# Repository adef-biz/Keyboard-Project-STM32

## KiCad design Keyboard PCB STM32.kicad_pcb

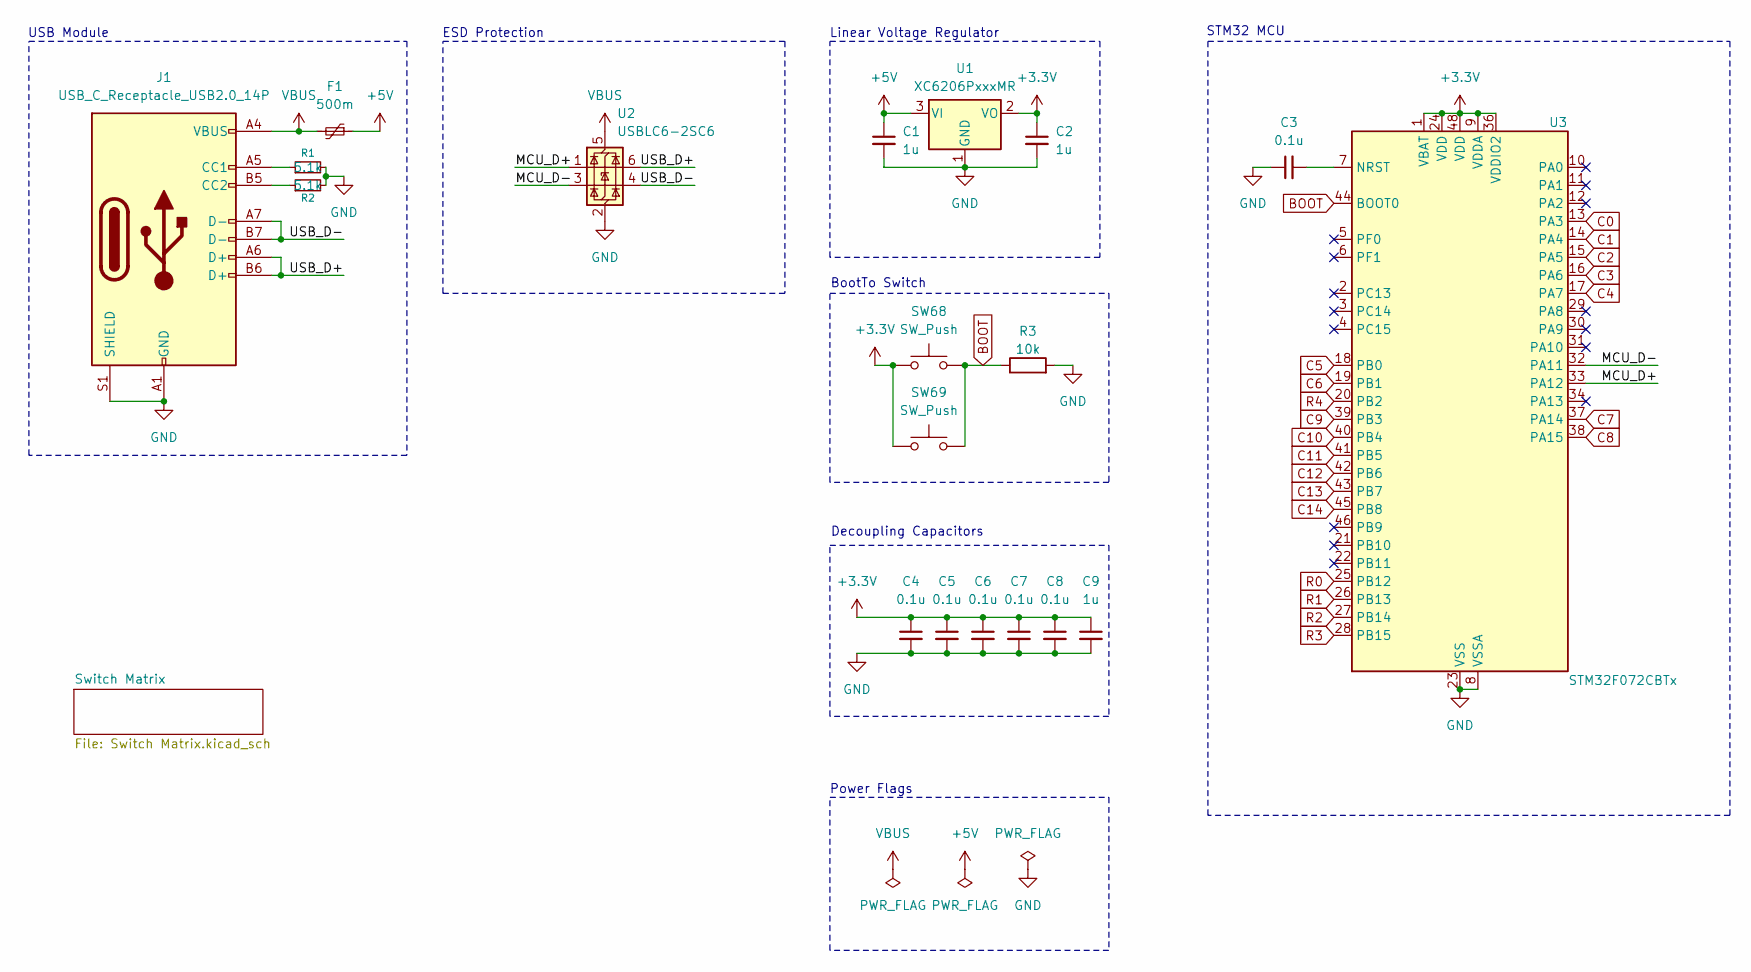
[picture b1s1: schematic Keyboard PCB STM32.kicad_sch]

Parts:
C1, C2, C9: 1u; C_0805_2012Metric
C3, C4, C5, C6, C7, C8: 0.1u; C_0805_2012Metric
F1: 500m; Fuse_1206_3216Metric
J1: USB_C_Receptacle_USB2.0_14P; USB_C_Receptacle_HRO_TYPE-C-31-M-12
R1, R2: 5.1k; R_0805_2012Metric
R3: 10k; R_0805_2012Metric
SW68: SW_Push; Panasonic_EVQPUL_EVQPUC
SW69: SW_Push; SW_Push_1P1T_XKB_TS-1187A
U1: XC6206PxxxMR; SOT-23-3
U2: USBLC6-2SC6; SOT-23-6
U3: STM32F072CBTx; LQFP-48_7x7mm_P0.5mm

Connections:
+3.3V: C2.1, C4.1, C5.1, C6.1, C7.1, C8.1, C9.1, SW68.1, SW69.1, U1.2 (VO), U3.1 (VBAT), U3.9 (VDDA), U3.24 (VDD), U3.36 (VDDIO2), U3.48 (VDD)
+5V: C1.1, F1.1, U1.3 (VI)
/MCU_D+: U2.1 (I/O1), U3.33 (PA12)
/MCU_D-: U2.3 (I/O2), U3.32 (PA11)
/USB_D+: J1.A6 (D+), J1.B6 (D+), U2.6 (I/O1)
/USB_D-: J1.A7 (D-), J1.B7 (D-), U2.4 (I/O2)
BOOT: R3.1, SW68.2, SW69.2, U3.44 (BOOT0)
C0: U3.13 (PA3); also elsewhere on the board
C1: U3.14 (PA4); also elsewhere on the board
C2: U3.15 (PA5); also elsewhere on the board
C3: U3.16 (PA6); also elsewhere on the board
C4: U3.17 (PA7); also elsewhere on the board
C5: U3.18 (PB0); also elsewhere on the board
C6: U3.19 (PB1); also elsewhere on the board
C7: U3.37 (PA14); also elsewhere on the board
C8: U3.38 (PA15); also elsewhere on the board
C9: U3.39 (PB3); also elsewhere on the board
C10: U3.40 (PB4); also elsewhere on the board
C11: U3.41 (PB5); also elsewhere on the board
C12: U3.42 (PB6); also elsewhere on the board
C13: U3.43 (PB7); also elsewhere on the board
C14: U3.45 (PB8); also elsewhere on the board
GND: C1.2, C2.2, C3.1, C4.2, C5.2, C6.2, C7.2, C8.2, C9.2, J1.A1 (GND), J1.A12 (GND), J1.B1 (GND), J1.B12 (GND), J1.S1 (SHIELD), R1.2, R2.2, R3.2, U1.1 (GND), U2.2 (GND), U3.8 (VSSA), U3.23 (VSS), U3.35 (VSS), U3.47 (VSS)
unnamed: J1.A5 (CC1), R1.1
unnamed: J1.B5 (CC2), R2.1
unnamed: C3.2, U3.7 (NRST)
R0: U3.25 (PB12); also elsewhere on the board
R1: U3.26 (PB13); also elsewhere on the board
R2: U3.27 (PB14); also elsewhere on the board
R3: U3.28 (PB15); also elsewhere on the board
R4: U3.20 (PB2); also elsewhere on the board
VBUS: F1.2, J1.A4 (VBUS), J1.A9 (VBUS), J1.B4 (VBUS), J1.B9 (VBUS), U2.5 (VBUS)

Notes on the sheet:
BootTo Switch
USB Module
ESD Protection
Linear Voltage Regulator
Decoupling Capacitors
Power Flags
STM32 MCU

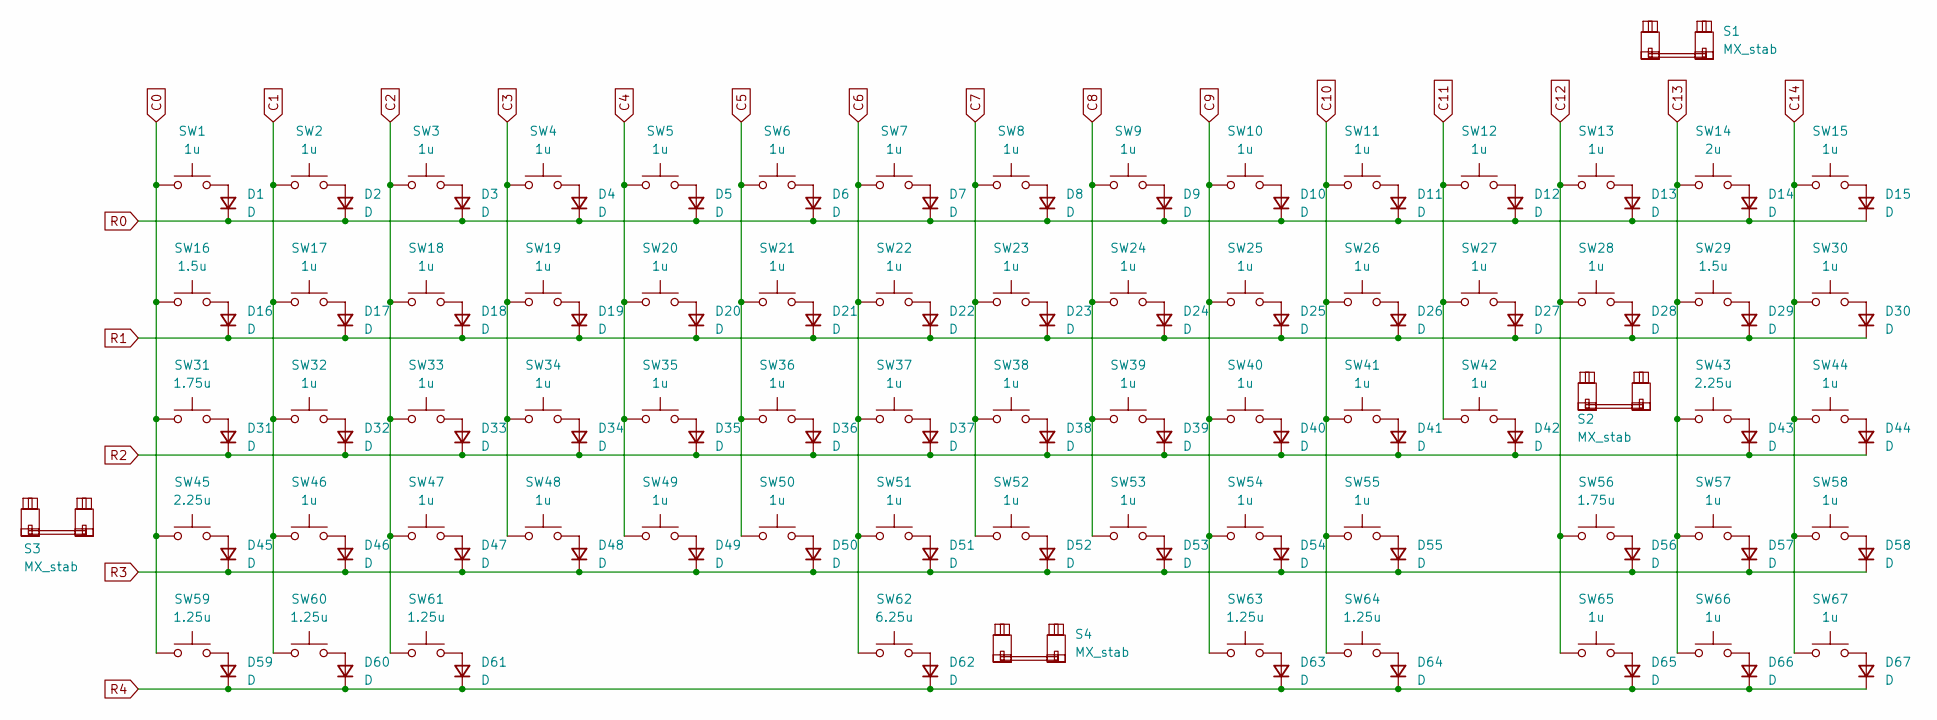
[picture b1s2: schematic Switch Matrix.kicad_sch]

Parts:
D1, D2, D3, D4, D5, D6, D7, D8, D9, D10, D11, D12, D13, D14, D15, D16, D17, D18, D19, D20, D21, D22, D23, D24, D25, D26, D27, D28, D29, D30, D31, D32, D33, D34, D35, D36, D37, D38, D39, D40, D41, D42, D43, D44, D45, D46, D47, D48, D49, D50, D51, D52, D53, D54, D55, D56, D57, D58, D59, D60, D61, D62, D63, D64, D65, D66, D67: D; D_SOD-123
S1: MX_stab; STAB_MX_2u
S2, S3: MX_stab; STAB_MX_2.25u
S4: MX_stab; STAB_MX_6.25u
SW1, SW2, SW3, SW4, SW5, SW6, SW7, SW8, SW9, SW10, SW11, SW12, SW13, SW15, SW17, SW18, SW19, SW20, SW21, SW22, SW23, SW24, SW25, SW26, SW27, SW28, SW30, SW32, SW33, SW34, SW35, SW36, SW37, SW38, SW39, SW40, SW41, SW42, SW44, SW46, SW47, SW48, SW49, SW50, SW51, SW52, SW53, SW54, SW55, SW57, SW58, SW65, SW66, SW67: 1u; SW_MX_1u
SW14: 2u; SW_MX_1u
SW16, SW29: 1.5u; SW_MX_1.5u
SW31, SW56: 1.75u; SW_MX_1.75u
SW43, SW45: 2.25u; SW_MX_1u
SW59, SW60, SW61, SW63, SW64: 1.25u; SW_MX_1.25u
SW62: 6.25u; SW_MX_1u

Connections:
C0: SW1.1, SW16.1, SW31.1, SW45.1, SW59.1; also elsewhere on the board
C1: SW2.1, SW17.1, SW32.1, SW46.1, SW60.1; also elsewhere on the board
C2: SW3.1, SW18.1, SW33.1, SW47.1, SW61.1; also elsewhere on the board
C3: SW4.1, SW19.1, SW34.1, SW48.1; also elsewhere on the board
C4: SW5.1, SW20.1, SW35.1, SW49.1; also elsewhere on the board
C5: SW6.1, SW21.1, SW36.1, SW50.1; also elsewhere on the board
C6: SW7.1, SW22.1, SW37.1, SW51.1, SW62.1; also elsewhere on the board
C7: SW8.1, SW23.1, SW38.1, SW52.1; also elsewhere on the board
C8: SW9.1, SW24.1, SW39.1, SW53.1; also elsewhere on the board
C9: SW10.1, SW25.1, SW40.1, SW54.1, SW63.1; also elsewhere on the board
C10: SW11.1, SW26.1, SW41.1, SW55.1, SW64.1; also elsewhere on the board
C11: SW12.1, SW27.1, SW42.1; also elsewhere on the board
C12: SW13.1, SW28.1, SW56.1, SW65.1; also elsewhere on the board
C13: SW14.1, SW29.1, SW43.1, SW57.1, SW66.1; also elsewhere on the board
C14: SW15.1, SW30.1, SW44.1, SW58.1, SW67.1; also elsewhere on the board
unnamed: D1.2 (A), SW1.2
unnamed: D2.2 (A), SW2.2
unnamed: D3.2 (A), SW3.2
unnamed: D4.2 (A), SW4.2
unnamed: D5.2 (A), SW5.2
unnamed: D6.2 (A), SW6.2
unnamed: D7.2 (A), SW7.2
unnamed: D8.2 (A), SW8.2
unnamed: D9.2 (A), SW9.2
unnamed: D10.2 (A), SW10.2
unnamed: D11.2 (A), SW11.2
unnamed: D12.2 (A), SW12.2
unnamed: D13.2 (A), SW13.2
unnamed: D14.2 (A), SW14.2
unnamed: D15.2 (A), SW15.2
unnamed: D16.2 (A), SW16.2
unnamed: D17.2 (A), SW17.2
unnamed: D18.2 (A), SW18.2
unnamed: D19.2 (A), SW19.2
unnamed: D20.2 (A), SW20.2
unnamed: D21.2 (A), SW21.2
unnamed: D22.2 (A), SW22.2
unnamed: D23.2 (A), SW23.2
unnamed: D24.2 (A), SW24.2
unnamed: D25.2 (A), SW25.2
unnamed: D26.2 (A), SW26.2
unnamed: D27.2 (A), SW27.2
unnamed: D28.2 (A), SW28.2
unnamed: D29.2 (A), SW29.2
unnamed: D30.2 (A), SW30.2
unnamed: D31.2 (A), SW31.2
unnamed: D32.2 (A), SW32.2
unnamed: D33.2 (A), SW33.2
unnamed: D34.2 (A), SW34.2
unnamed: D35.2 (A), SW35.2
unnamed: D36.2 (A), SW36.2
unnamed: D37.2 (A), SW37.2
unnamed: D38.2 (A), SW38.2
unnamed: D39.2 (A), SW39.2
unnamed: D40.2 (A), SW40.2
unnamed: D41.2 (A), SW41.2
unnamed: D42.2 (A), SW42.2
unnamed: D43.2 (A), SW43.2
unnamed: D44.2 (A), SW44.2
unnamed: D45.2 (A), SW45.2
unnamed: D46.2 (A), SW46.2
unnamed: D47.2 (A), SW47.2
unnamed: D48.2 (A), SW48.2
unnamed: D49.2 (A), SW49.2
unnamed: D50.2 (A), SW50.2
unnamed: D51.2 (A), SW51.2
unnamed: D52.2 (A), SW52.2
unnamed: D53.2 (A), SW53.2
unnamed: D54.2 (A), SW54.2
unnamed: D55.2 (A), SW55.2
unnamed: D56.2 (A), SW56.2
unnamed: D57.2 (A), SW57.2
unnamed: D58.2 (A), SW58.2
unnamed: D59.2 (A), SW59.2
unnamed: D60.2 (A), SW60.2
unnamed: D61.2 (A), SW61.2
unnamed: D62.2 (A), SW62.2
unnamed: D63.2 (A), SW63.2
unnamed: D64.2 (A), SW64.2
unnamed: D65.2 (A), SW65.2
unnamed: D66.2 (A), SW66.2
unnamed: D67.2 (A), SW67.2
R0: D1.1 (K), D2.1 (K), D3.1 (K), D4.1 (K), D5.1 (K), D6.1 (K), D7.1 (K), D8.1 (K), D9.1 (K), D10.1 (K), D11.1 (K), D12.1 (K), D13.1 (K), D14.1 (K), D15.1 (K); also elsewhere on the board
R1: D16.1 (K), D17.1 (K), D18.1 (K), D19.1 (K), D20.1 (K), D21.1 (K), D22.1 (K), D23.1 (K), D24.1 (K), D25.1 (K), D26.1 (K), D27.1 (K), D28.1 (K), D29.1 (K), D30.1 (K); also elsewhere on the board
R2: D31.1 (K), D32.1 (K), D33.1 (K), D34.1 (K), D35.1 (K), D36.1 (K), D37.1 (K), D38.1 (K), D39.1 (K), D40.1 (K), D41.1 (K), D42.1 (K), D43.1 (K), D44.1 (K); also elsewhere on the board
R3: D45.1 (K), D46.1 (K), D47.1 (K), D48.1 (K), D49.1 (K), D50.1 (K), D51.1 (K), D52.1 (K), D53.1 (K), D54.1 (K), D55.1 (K), D56.1 (K), D57.1 (K), D58.1 (K); also elsewhere on the board
R4: D59.1 (K), D60.1 (K), D61.1 (K), D62.1 (K), D63.1 (K), D64.1 (K), D65.1 (K), D66.1 (K), D67.1 (K); also elsewhere on the board

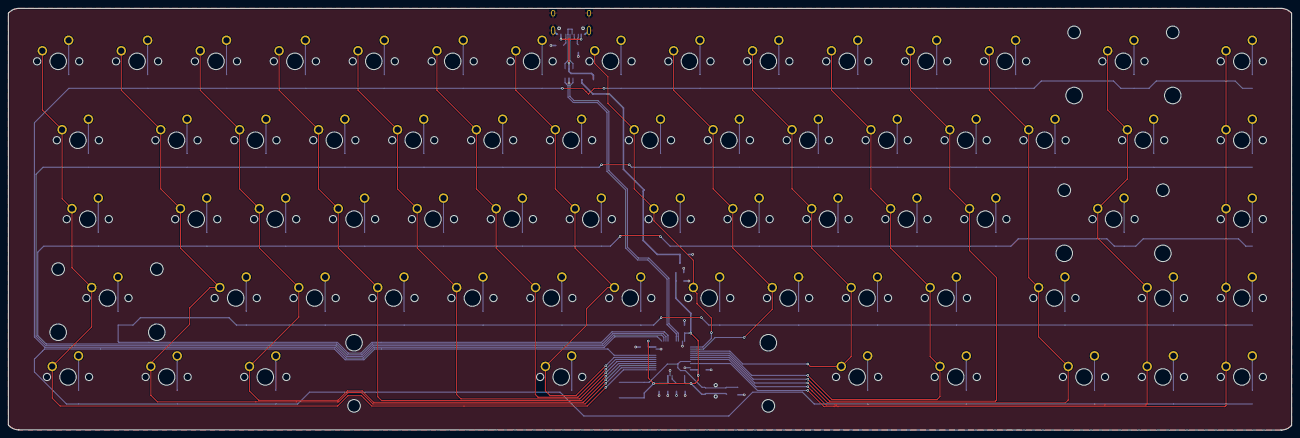
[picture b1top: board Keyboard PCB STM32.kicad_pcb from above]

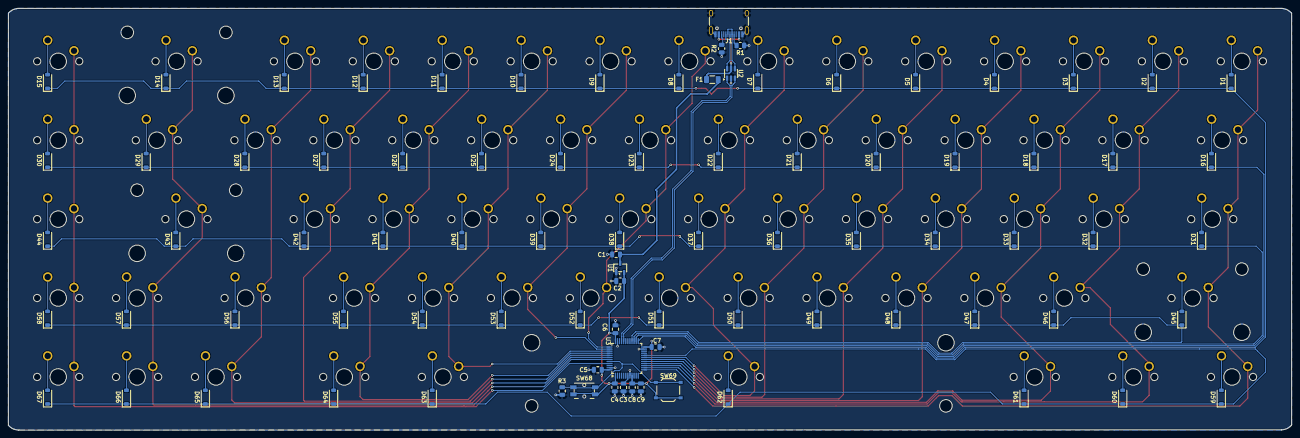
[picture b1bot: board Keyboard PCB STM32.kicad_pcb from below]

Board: 2 copper layers, 309.8 x 101.8 mm, 157 parts (86 on the bottom side), 99 nets.

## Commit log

2026-03-24 Update to ESD protection
    Changed ESD from SRV05-4 to USBLC6-2SC6
